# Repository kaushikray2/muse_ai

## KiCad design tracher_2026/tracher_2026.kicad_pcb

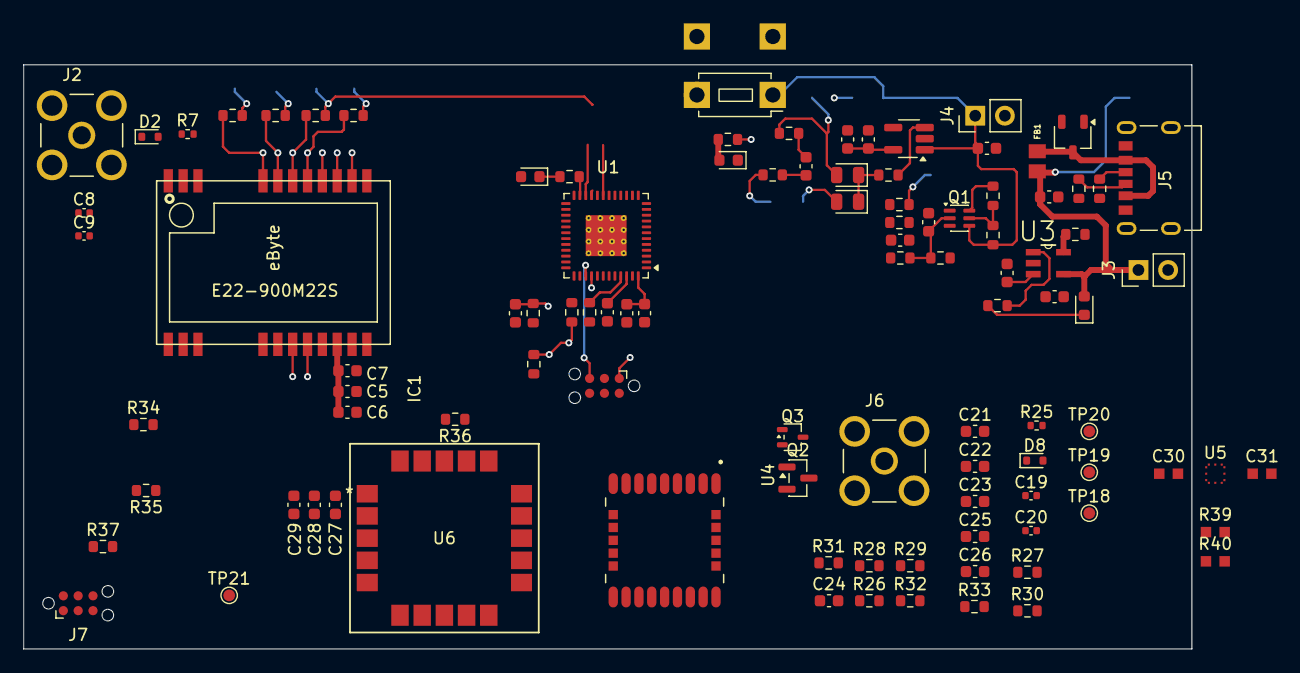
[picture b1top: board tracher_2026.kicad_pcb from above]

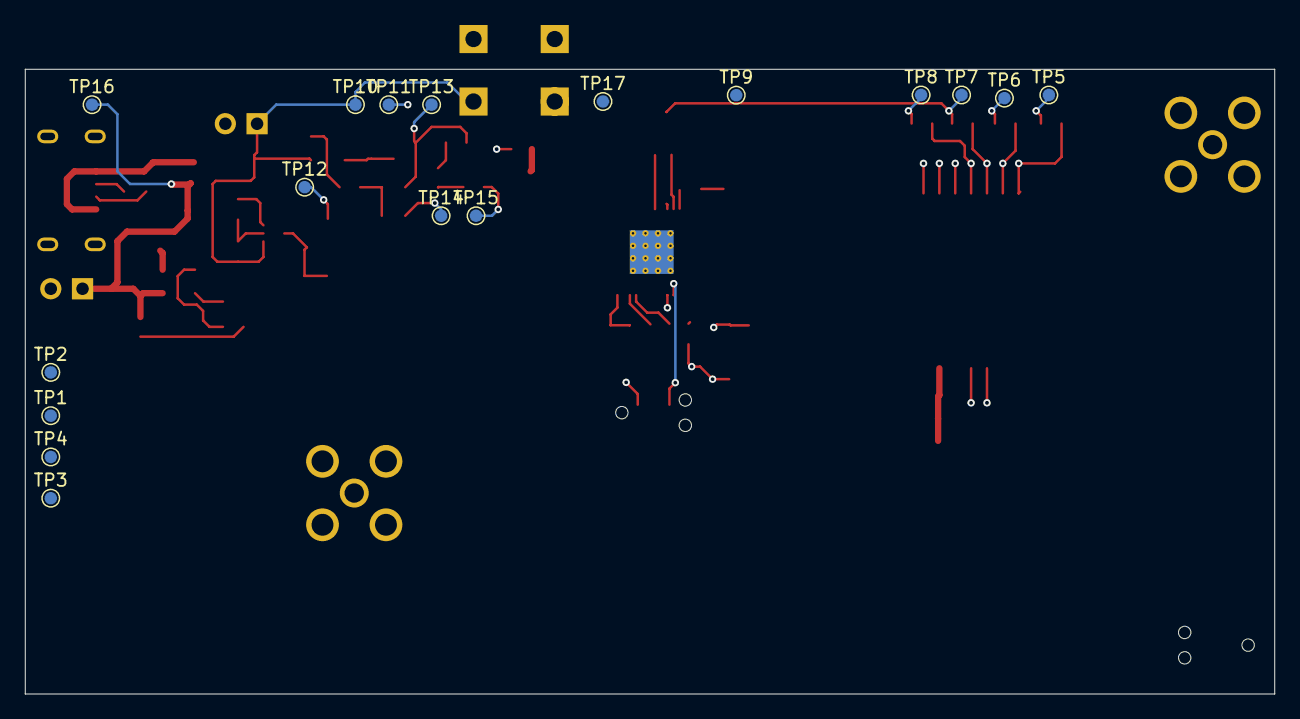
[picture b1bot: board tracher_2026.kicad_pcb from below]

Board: 4 copper layers, 100.0 x 50.0 mm, 118 parts (17 on the bottom side), 69 nets.

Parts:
C1, C5, C11, C21, C25, C27: 100nF/16V; C_0603_1608Metric
C2, C4, C14: 10nF/16V; C_0603_1608Metric
C3, C24, C26: 1uF/16V; C_0603_1608Metric
C6, C22, C28: 33pF/16V; C_0603_1608Metric
C7, C16, C17, C23, C29: 10uF/16v; C_0603_1608Metric
C8, C9, C19, C20: 0nF/16V; C_0402_1005Metric
C10, C15, C18: 2.2uF/16V; C_0603_1608Metric
C12: 10uF/16V; C_0603_1608Metric
C13: 1nF/16V; C_0603_1608Metric
C30, C31: 100nF; C_0603_1608Metric
D1, D4, D6: LED; LED_0603_1608Metric
D2, D8: ESD5Zxx; D_SOD-523
D3, D5: 1N4148; D_0805_2012Metric
D7: TSOT-23
FB1: MPZ2012S601ATD25; BEADC2012X105N
IC1: E22-900M22S
J1, J7: TC2030; Tag-Connect_TC2030-IDC-NL_2x03_P1.27mm_Vertical
J2, J6: RFPC-SMA28-F; GRADCONN_RFPC-SMA28-F
J3: Charger Connector; PinHeader_1x02_P2.54mm_Vertical
J4: Battery Connector; PinHeader_1x02_P2.54mm_Vertical
J5: UJC-H-G-SMT-2-P6-TR; SAMESKY_UJC-H-G-SMT-2-P6-TR
Q1: MBT3946DW1T1; SOT-363_SC-70-6
Q2: BSS83P; SOT-23
Q3: 2SC4213; SOT-323_SC-70
R1, R5, R18, R19: 1K/5%; R_0603_1608Metric
R2, R4, R27, R30, R36: 10K/5%; R_0603_1608Metric
R3: 220/5%; R_0603_1608Metric
R6: 10E/5%; R_0603_1608Metric
R7, R25: 0E/5%; R_0402_1005Metric
R8, R9, R10, R32, R33, R37: 22E/5%; R_0603_1608Metric
R11, R12, R13, R20: 100K/5%; R_0603_1608Metric
R14, R16: 22K/1%; R_0603_1608Metric
R15: 470K/5%; R_0603_1608Metric
R17: 470E/5%; R_0603_1608Metric
R21: 2K/5%; R_0603_1608Metric
R22, R29: 220E/5%; R_0603_1608Metric
R23, R24: 5.1K/5%; R_0603_1608Metric
R26: 0E/5%; R_0603_1608Metric
R28: 4.7K/5%; R_0603_1608Metric
R31: 51K/5%; R_0603_1608Metric
R34: 2.2K/5%; R_0603_1608Metric
R35: 8.2K/5%; R_0603_1608Metric
R39, R40: 4.7K; R_0603_1608Metric
SW1: SW_PUSH_6mm_H5mm_4pin
TP1, TP2, TP3, TP4, TP5, TP6, TP7, TP8, TP9, TP10, TP11, TP12, TP13, TP14, TP15, TP16, TP17, TP18, TP19, TP20, TP21: TestPoint_Pad_D1.0mm
U1: QFN-48-1EP_7x7mm_P0.5mm_EP3.5x3.5mm_ThermalVias
U2: SOT-23-5_HandSoldering
U3: MCP73831T-2ACI_OT; SOT95P280X145-5N
U4: LC76G; XCVR_LC76G
U5: LSM303AGRTR; LGA12R50P_200X200X100
U6: SAM-M10Q-00B; SAM-M10Q_UBL

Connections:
+3.3V: C1.1, C2.1, C5.1, C6.1, C7.1, C11.1, C12.1, C24.1, C25.1, C26.1, C27.1, C28.1, C29.1, C31.1, D1.2 (A), IC1.9 (VCC), J1.2, J7.2, Q2.2 (S), R1.2, R4.1, R5.1, R6.2, R22.2, R26.1, R27.1, R28.1, R36.1, R39.2, R40.2, TP1.1 (1_1), TP5.1 (1_1), TP11.1 (1_1), U1.48 (VDD), U2.5 (OUT), U4.6 (V_BCKP), U5.2, U5.3, U5.9, U5.10, U6.2 (V_IO), U6.17 (VCC)
+5V: C16.1, C18.1, D4.2 (A), FB1.1, J3.1, TP16.1 (1_1), U3.4 (VDD)
/GNSS/GNSS_RF_IN: C20.1, R25.2, U4.11 (RF_IN)
/GNSS/MCU_GNSS_RXD: J7.3, U6.14 (RXD)
/GNSS/MCU_GNSS_TXD: J7.6, R37.1
/MCU_BUTTON_SENSE: R34.1, R35.2, U1.2 (P61/EO61/CCD05/SDAA0)
/MCU_BattVolt: C14.1, R14.1, R16.2, TP12.1 (1_1), U1.32 (P20/ANI0/AV)
/MCU_BattVolt_EN: R13.2, U1.1 (P60/EO60/CCD04/SCLA0)
/MCU_GNSS_3DFIX: U1.11 (P70/TS02/RIN0/KR0/SCK21/SCL21), U4.23 (3D_FIX)
/MCU_GNSS_ANT_ON: U1.10 (P71/TS03/KR1/SI21/SDA21/RxDA0), U4.13 (ANT_ON)
/MCU_GNSS_AP_REQ: U1.9 (P72/TS04/KR2/SO21/TxDA0), U4.5 (~AP_REQ)
/MCU_GNSS_EN: R31.1, U1.8 (P73/TS05/KR3/SO01)
/MCU_GNSS_GEOFENCE: U1.7 (P74/TS06/KR4/INTP8/SI01/SDA01), U4.21 (GEOFENCE)
/MCU_GNSS_JAM_IND: U1.6 (P75/TS07/KR5/INTP9/SCK01/SCL01), U4.22 (JAM_IND)
/MCU_GNSS_RESET: R27.2, R36.2, U1.4 (P63/CCD07/SDAA1), U4.9 (~RESET), U6.18 (RESET_N)
/MCU_GNSS_RX: R33.1, U1.34 (P01/TS27/EI01/EO01/TO00/RxD1)
/MCU_GNSS_TX: R32.1, U1.35 (P00/TS26/EI00/TI00/TxD1)
/MCU_I2C_SCL: R39.1, U5.1
/MCU_I2C_SDA: R40.1, U5.4
/MCU_SYS_EN: D3.2 (A), TP14.1 (1_1), U1.3 (P62/CCD06/SCLA1)
/Micro+LORA/MCU_D_RX: J1.3, U1.16 (P16/EO16/CCD00/TI01/TO01/INTP5/(RxD0))
/Micro+LORA/MCU_D_TX: J1.6, U1.15 (P17/EO17/CCD01/TI02/TO02/(TxD0))
/Micro+LORA/MCU_LED: R3.1, U1.23 (P146)
/Micro+LORA/MCU_LORA_BUSY: IC1.14 (BUSY), U1.36 (P140/PCLBUZ0/INTP6)
/Micro+LORA/MCU_LORA_DIO1: IC1.13 (DIO1), TP9.1 (1_1), U1.5 (P31/TS01/EI31/TI03/TO03/INTP4)
/Micro+LORA/MCU_LORA_MISO: R10.2, TP8.1 (1_1), U1.21 (P11/EI11/EO11/SI00/RxD0/TOOLRxD/SDA00/(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)
/Micro+LORA/MCU_LORA_MOSI: R9.2, TP7.1 (1_1), U1.20 (P12/EI12/EO12/SO00/TxD0/TOOLTxD/(TI05)/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)
/Micro+LORA/MCU_LORA_NSS: IC1.19 (NSS), R6.1, U1.19 (P13/IVREF1/EO13/TxD2/SO20/(SDAA0)/(TI04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)
/Micro+LORA/MCU_LORA_RST: IC1.15 (NRST), U1.25 (P27/ANI7/TS25)
/Micro+LORA/MCU_LORA_RXEN: IC1.6 (RXEN), U1.26 (P26/ANI6/TS24)
/Micro+LORA/MCU_LORA_SCK: R8.2, TP6.1 (1_1), U1.22 (P10/EI10/EO10/SCK00/SCL00/(TI07)/(TO07))
/Micro+LORA/MCU_LORA_TXEN: IC1.7 (TXEN), U1.27 (P25/ANI5/TS23)
/Micro+LORA/MCU_RST: C4.1, J1.1, R4.2, TP2.1 (1_1), U1.40 (RESET)
/Micro+LORA/MCU_TOOL: J1.5, R5.2, TP3.1 (1_1), U1.39 (P40/TOOL0)
/Power/LDO_EN: R19.1, R20.2, TP15.1 (1_1), U2.3 (EN)
GND: C1.2, C2.2, C3.2, C4.2, C5.2, C6.2, C7.2, C8.2, C9.2, C10.2, C11.2, C12.2, C13.2, C14.2, C15.2, C16.2, C17.2, C18.2, C19.2, C20.2, C21.2, C22.2, C23.2, C25.2, C26.2, C27.2, C28.2, C29.2, C30.2, C31.2, D2.2 (A), D6.1 (K), D7.1 (Anode), D8.2 (A), IC1.1 (GND), IC1.2, IC1.3, IC1.4, IC1.5, IC1.10, IC1.11, IC1.12, IC1.20, IC1.22, J1.4, J2.G1, J2.G2, J2.G3, J2.G4, J3.2, J4.2, J5.A12 (GND), J5.B12 (GND__1), J5.SH1 (SHIELD), J5.SH2 (SHIELD__1), J5.SH3 (SHIELD__2), J5.SH4 (SHIELD__3), J6.G1, J6.G2, J6.G3, J6.G4, J7.4, Q1.1 (E1), Q3.2 (E), R2.2, R15.2, R16.1, R20.1, R21.2, R23.1, R24.1, R30.2, R35.1, TP4.1 (1_1), U1.47 (Vss), U1.49, U2.2 (GND), U3.2 (VSS), U4.1 (GND), U4.10 (GND__1), U4.12 (GND__2), U4.28 (GND__3), U5.6, U5.8, U6.1 (GND), U6.4 (GND), U6.5 (GND), U6.6 (GND), U6.10 (GND), U6.11 (GND), U6.15 (GND), U6.16 (GND), U6.20 (GND)
unnamed: C15.1, R18.2
unnamed: D1.1 (K), R3.2
unnamed: C9.1, D2.1 (K), J2.1, R7.1
unnamed: D3.1 (K), D5.1 (K), R19.2
unnamed: D4.1 (K), R17.1
unnamed: D5.2 (A), R18.1, R34.2, SW1.3 (B_1), SW1.4 (B_2), TP13.1 (1_1)
unnamed: D6.2 (A), R22.1
unnamed: D7.3 (Cathode), FB1.2, J5.A9 (VBUS), J5.B9 (VBUS__1)
unnamed: C19.1, D8.1 (K), J6.1, R25.1
unnamed: C8.1, IC1.21 (ANT), R7.2
unnamed: IC1.16 (MISO), R10.1
unnamed: IC1.17 (MOSI), R9.1
unnamed: IC1.18 (SCK), R8.1
unnamed: J5.A5 (CC1), R23.2
unnamed: J5.B5 (CC2), R24.2
unnamed: C13.1, Q1.2 (B1), R13.1, R15.1
unnamed: Q1.6 (C1), R12.2
unnamed: Q1.5 (B2), R11.2, R12.1
unnamed: Q1.3 (C2), R14.2
unnamed: C21.1, C22.1, C23.1, Q2.3 (D), R26.2, TP18.1 (1_1), U4.8 (VCC), U4.14 (VDD_RF)
unnamed: C24.2, Q2.1 (G), R29.1
unnamed: Q3.1 (B), R31.2
unnamed: Q3.3 (C), R28.2, R29.2
unnamed: R2.1, U1.45 (P121/X1/VBAT/EI121)
unnamed: C3.1, U1.46 (REGC)
unnamed: R21.1, U3.5 (PROG)
unnamed: R17.2, U3.1 (STAT)
unnamed: R30.1, U4.24 (D_SEL)
unnamed: R33.2, TP20.1 (1_1), U4.3 (RXD)
unnamed: R32.2, TP19.1 (1_1), U4.2 (TXD)
unnamed: C30.1, U5.5
unnamed: R37.2, TP21.1 (1_1), U6.13 (TXD)
V_BAT+: C10.1, C17.1, J4.1, Q1.4 (E2), R11.1, SW1.1 (A_1), SW1.2 (A_2), TP10.1 (1_1), TP17.1 (1_1), U2.1 (IN), U3.3 (VBAT)

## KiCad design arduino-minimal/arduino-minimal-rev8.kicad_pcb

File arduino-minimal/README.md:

# Minimal Arduino (ATmega328P-AU) — KiCad schematic

Minimal all-SMD Arduino-compatible board. ATmega328P-AU (TQFP-32),
internal 8 MHz oscillator (no crystal).

## Revisions
- **rev8 (current, 2026-10-08)** — Regenerated with correct KiCad
  coordinate transform. Opens in KiCad 10, ERC clean (see below),
  netlist verified. **Use this one.**
- rev7 — Fixed file-format bugs (unit names, lib_symbols headers,
  `(unlocked)`), loads in KiCad, but wires were routed to wrong
  pin positions (see "coordinate bug" below). Superseded by rev8.
- rev6 and earlier — do not open in KiCad (format bugs). Superseded.

## Circuit
- **U1** ATmega328P-AU — official KiCad `MCU_Microchip_ATmega:ATmega48PV-10A` symbol,
  Value set to ATmega328P-AU, footprint `Package_QFP:TQFP-32_7x7mm_P0.8mm`
- **R1** 10 kΩ 0805 — RESET pull-up to VCC
- **C1** 100 nF 0805 — VCC decoupling
- **C2** 100 nF 0805 — AVCC decoupling (AVCC tied to VCC per datasheet)
- **C3** 100 nF 0805 — AREF decoupling
- **J1** 3-pin 2.54 mm SMD header — pin1 RX (PD0), pin2 TX (PD1), pin3 GND
- **J2** 2-pin 2.54 mm SMD header — pin1 +5V in, pin2 GND
- PB6/PB7: no-connect (no crystal)

All symbols are official KiCad library symbols embedded in the file.

## Fuses (internal 8 MHz)
- LF `0xE2`, HF `0xDA`, EF `0x05`

## The coordinate bug (rev6/7)
KiCad's symbol libraries are authored Y-UP, but the schematic sheet is
Y-DOWN. On placement KiCad converts: pin (px, py) on a symbol at (X, Y)
rotated t° clockwise lands at
`(X + px·cos t − py·sin t, Y − px·sin t − py·cos t)`.
The rev6/7 generator wired to `(X+px, Y+py)` (no conversion), so in KiCad
every wire missed its pin (89 ERC violations, all "pin not connected").
`generate_schematic.py` now uses `kicad_pin()` with the correct transform;
rev8 was re-routed for it (VCC bus along the top, GND below).

## ERC status (2026-10-08, rev8, KiCad 10.0.6 native ERC)
Netlist verified correct: VCC (U1.4/U1.6/AVCC/C1/C2/R1/J2.1),
GND (U1.3/U1.5/U1.21/C1/C2/C3/J1.3/J2.2), RX (PD0↔J1.1),
TX (PD1↔J1.2), RESET pull-up, AREF decoupling.
Remaining ERC items are benign/expected:
- 20× unconnected pins — unused GPIOs (PD2-PD7, PB0-PB5, PC0-PC5,
  ADC6/ADC7), as intended for a minimal board
- `power_pin_not_driven` on VCC/GND — normal without PWR_FLAG symbols
- `endpoint_off_grid` — library pins not on 1.27mm grid; they still connect
- `lib_symbol_issues` / `footprint_link_issues` — headless environment
  lacks library table config; symbols/footprints are embedded/assigned

## Files
- `generate_schematic.py` — generates `arduino-minimal-rev8.kicad_sch`
- `extract_symbols.py` — pulls official symbols from a local kicad-symbols checkout
  (unit sub-symbols must keep short names, e.g. `R_0_1` not `Device:R_0_1`;
  no version/generator lines inside `lib_symbols`)
- `validate.py` — sexp balance, connectivity, geometry, rotation-aware checks
- `erc_check.py` — standalone ERC (now uses the correct Y-up→Y-down transform)
- `arduino-minimal-rev8.kicad_sch` / `.kicad_pro` — deliverables (KiCad 9/10)
- `rev8.pdf` / `rev8-preview.png` — rendered schematic

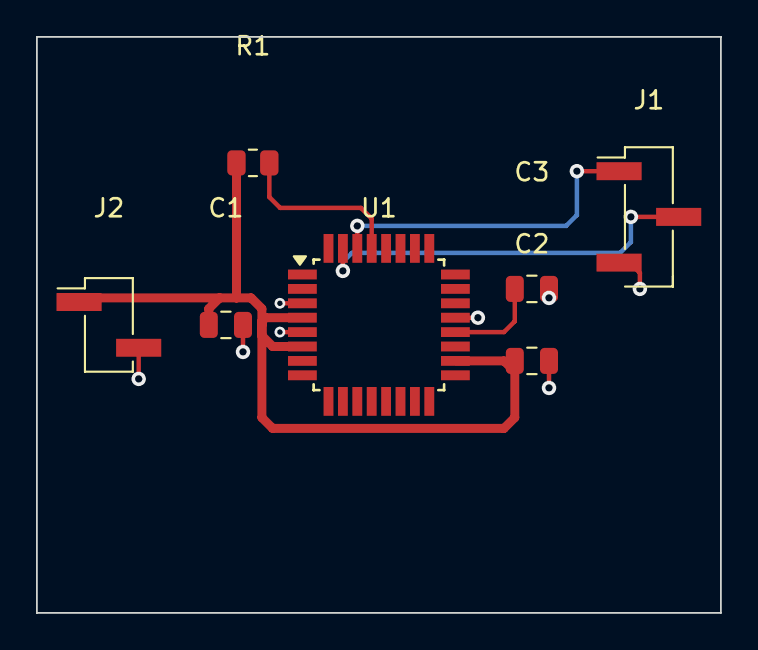
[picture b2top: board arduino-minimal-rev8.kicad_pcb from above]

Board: 2 copper layers, 38.0 x 32.0 mm, 7 parts (0 on the bottom side), 6 nets.

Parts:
C1, C2, C3: 100nF; C_0805_2012Metric
J1: Conn_01x03; PinHeader_1x03_P2.54mm_Vertical_SMD_Pin1Left
J2: Conn_01x02; PinHeader_1x02_P2.54mm_Vertical_SMD_Pin1Left
R1: 10k; R_0805_2012Metric
U1: ATmega328P-AU; TQFP-32_7x7mm_P0.8mm

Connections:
/RX: J1.1, U1.30
/TX: J1.2, U1.31
GND: C1.2, C2.2, C3.2, J1.3, J2.2, U1.3, U1.5, U1.21
unnamed: C3.1, U1.20
unnamed: R1.2, U1.29
VCC: C1.1, C2.1, J2.1, R1.1, U1.4, U1.6, U1.18

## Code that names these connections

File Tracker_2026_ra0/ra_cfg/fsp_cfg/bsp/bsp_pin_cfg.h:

/* generated configuration header file - do not edit */
#ifndef BSP_PIN_CFG_H_
#define BSP_PIN_CFG_H_
#include "r_ioport.h"

/* Common macro for FSP header files. There is also a corresponding FSP_FOOTER macro at the end of this file. */
FSP_HEADER

#define MCU_LORA_RXEN (BSP_IO_PORT_00_PIN_14)
#define MCU_LORA_NSS (BSP_IO_PORT_00_PIN_15)
#define MCU_LORA_SI (BSP_IO_PORT_01_PIN_00)
#define MCU_LORA_SO (BSP_IO_PORT_01_PIN_01)
#define MCU_LORA_SCK (BSP_IO_PORT_01_PIN_02)
#define MCU_LED (BSP_IO_PORT_01_PIN_03)
#define MCU_GNSS_TXD (BSP_IO_PORT_01_PIN_09)
#define MCU_GNSS_RXD (BSP_IO_PORT_01_PIN_10)
#define MCU_LORA_RST (BSP_IO_PORT_01_PIN_12)
#define MCU_LORA_TXEN (BSP_IO_PORT_02_PIN_01)
#define MCU_RST (BSP_IO_PORT_02_PIN_06)
#define MCU_LORA_DIO1 (BSP_IO_PORT_02_PIN_07)
#define MCU_LORA_BUSY (BSP_IO_PORT_02_PIN_08)

#define PIN_SCK00 (BSP_IO_PORT_01_PIN_02)
#define CFG_SCK00 ((uint32_t) IOPORT_CFG_PERIPHERAL_PIN | (uint32_t) IOPORT_PERIPHERAL_SAU3_OUT)

#define PIN_SO00 (BSP_IO_PORT_01_PIN_01)
#define CFG_SO00 ((uint32_t) IOPORT_CFG_PERIPHERAL_PIN | (uint32_t) IOPORT_PERIPHERAL_SAU3_OUT)

extern const ioport_cfg_t g_bsp_pin_cfg; /* R7FA0E2094CFJ.pincfg */

void BSP_PinConfigSecurityInit();

/* Common macro for FSP header files. There is also a corresponding FSP_HEADER macro at the top of this file. */
FSP_FOOTER
#endif /* BSP_PIN_CFG_H_ */
